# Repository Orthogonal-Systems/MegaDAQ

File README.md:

# MegaDAQ
Data acquisition shield for VMEMega system compatible with arduino mega boards. 16 12b ADCs and 12 12b DACs.

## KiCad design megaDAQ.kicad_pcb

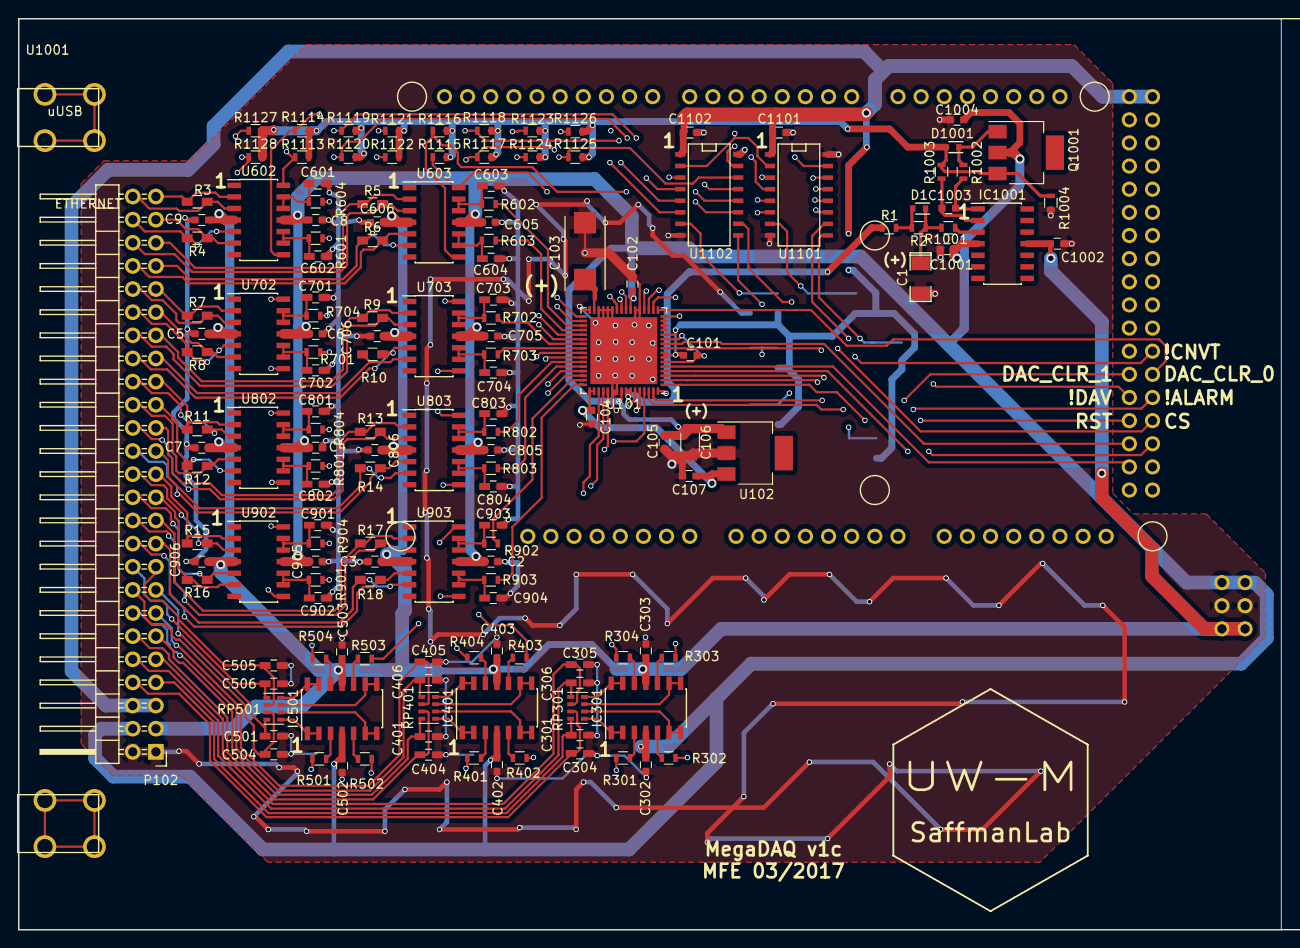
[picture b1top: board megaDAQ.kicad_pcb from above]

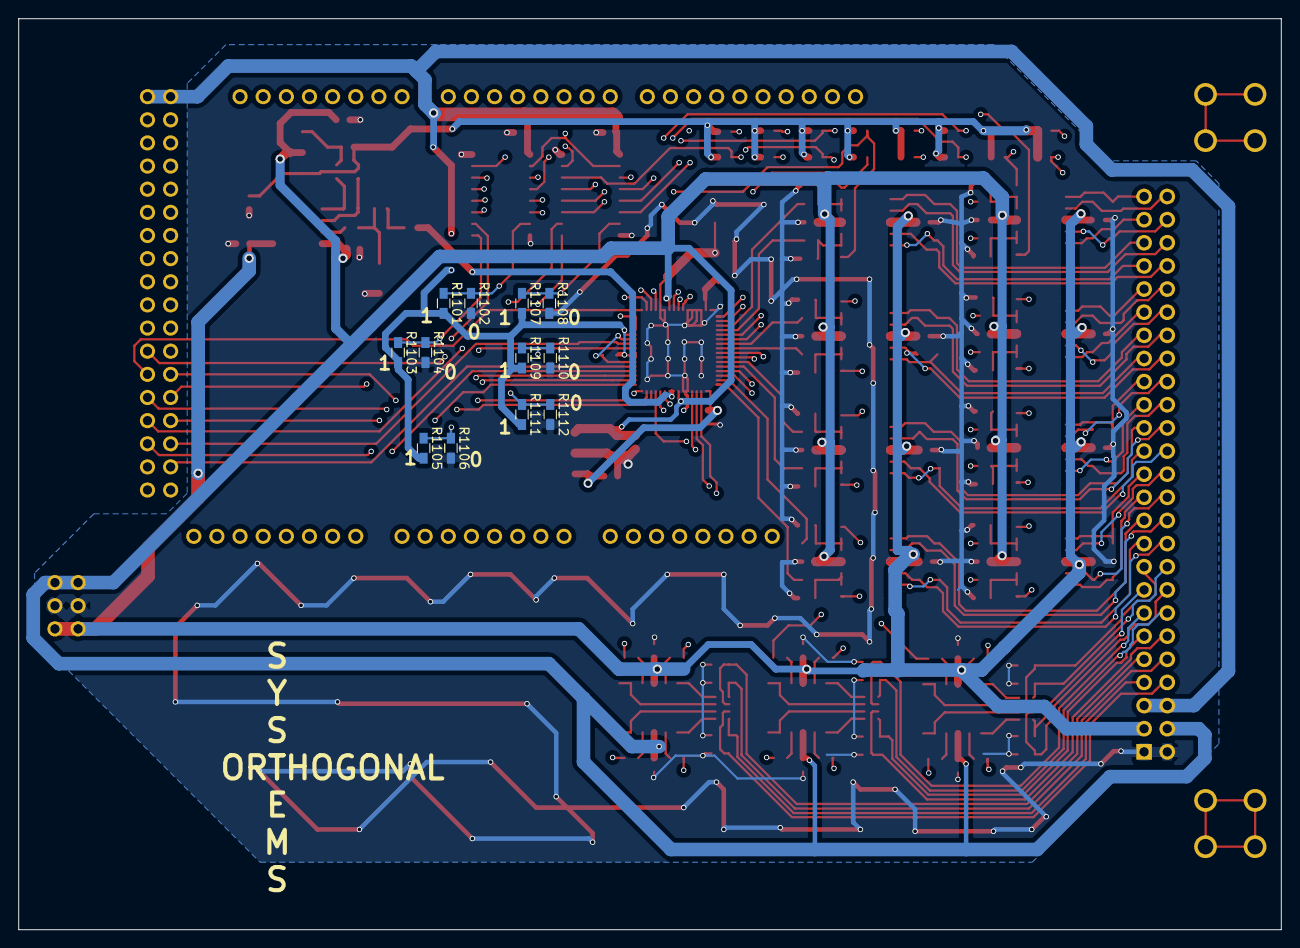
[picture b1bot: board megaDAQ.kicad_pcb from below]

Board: 4 copper layers, 138.6 x 100.0 mm, 168 parts (12 on the bottom side), 161 nets.

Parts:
C1: 15u; SMD-1206_Pol
C2, C3, C4, C5, C6, C7, C8, C9, C101, C102, C104, C105, C107, C302, C303, C402, C403, C502, C503, C605, C606, C705, C706, C805, C806, C905, C906: 0.1u; C_0603
C103: 470u; TantalC_SizeD_EIA-7343_Reflow
C106: 0.33u; C_1206
C301, C304, C305, C306, C401, C404, C405, C406, C501, C504, C505, C506: 10n; C_0603_HandSoldering
C601, C602, C603, C604, C701, C702, C703, C704, C801, C802, C803, C804, C901, C902, C903, C904: 2n; C_0603_HandSoldering
C1001, C1002, C1004, C1101, C1102: 100n; C_0603
C1003: 1n; C_0603
D1, D1001: BAS16; SOD-523
IC301, IC401, IC501, IC1001: MC33079D; SOIC-14_3.9x8.7mm_Pitch1.27mm
P102: CONN_02X25; Pin_Header_Angled_2x25
P105, P106: CONN_01X01; keystone_7773
Q1001: PZT2222A; SOT-223
R1: 698; R_0603
R2, R1004, R1113, R1114, R1115, R1116, R1117, R1118, R1119, R1120, R1121, R1122, R1123, R1124, R1125, R1126, R1127, R1128: 10k; R_0603
R3, R4, R5, R6, R7, R8, R9, R10, R11, R12, R13, R14, R15, R16, R17, R18, R1102, R1103, R1105, R1108, R1109, R1112: DNI; R_0603_HandSoldering
R301, R302, R303, R304, R401, R402, R403, R404, R501, R502, R503, R504, R601, R602, R603, R604, R701, R702, R703, R704, R801, R802, R803, R804, R901, R902, R903, R904, R1001, R1002: 100; R_0603
R1003: 500; R_0603
R1101, R1104, R1106, R1107, R1110, R1111: 0; R_0603_HandSoldering
RP301, RP401, RP501: R_PACK4; R_Cat16-4
U101: AMC7812SPAPR; QFN-64-1EP_9x9mm_Pitch0.5mm
U102: LM78M05CT; SOT-223
U602, U603, U702, U703, U802, U803, U902, U903: diffamp; SOIC-14_3.9x8.7mm_Pitch1.27mm
U1001: VMEMega_no-ICSP2; VMEMegaShield_no-ICSPs
U1101, U1102: TPIC2810; SO-16-N

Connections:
+2V5: R1.2, U101.57, U101.58
+5V: C101.1, C1101.1, C1102.1, P102.5, P102.6, R1101.2, R1103.2, R1105.2, R1107.2, R1109.2, R1111.2, U101.7, U101.8, U101.12, U1001.51, U1001.52, U1101.1, U1102.1
+15V: C2.1, C4.1, C6.1, C8.1, C102.1, C105.1, C106.1, C302.1, C402.1, C502.1, C605.1, C705.1, C805.1, C905.1, C1001.2, C1004.2, IC301.4, IC401.4, IC501.4, IC1001.4, P102.4, Q1001.2, U101.23, U101.56, U102.1, U602.11, U603.11, U702.11, U703.11, U802.11, U803.11, U902.11, U903.11, U1001.87
-15V: C3.2, C5.2, C7.2, C9.2, C303.2, C403.2, C503.2, C606.2, C706.2, C806.2, C906.2, C1002.2, IC301.11, IC401.11, IC501.11, IC1001.11, P102.3, U602.4, U603.4, U702.4, U703.4, U802.4, U803.4, U902.4, U903.4, U1001.89
/!ALARM: U101.62, U1001.78
/!AMC_CS: U101.9, U1001.80
/!AMC_RST: U101.1, U1001.79
/!CNVT: U101.3, U1001.74
/!DAC_CLR_0: U101.17, U1001.76
/!DAC_CLR_1: U101.63, U1001.75
/!DAV: U101.2, U1001.77
/ADC_0: R604.2, U101.33
/ADC_1: R601.2, U101.34
/ADC_2: R602.2, U101.35
/ADC_3: R603.2, U101.36
/ADC_4: R704.2, U101.37
/ADC_5: R701.2, U101.38
/ADC_6: R702.2, U101.39
/ADC_7: R703.2, U101.40
/ADC_8: R804.2, U101.41
/ADC_9: R801.2, U101.42
/ADC_10: R802.2, U101.43
/ADC_11: R803.2, U101.44
/ADC_12: R904.2, U101.45
/ADC_13: R901.2, U101.46
/ADC_14: R902.2, U101.47
/ADC_15: R903.2, U101.48
/ADC_REF: D1001.2, Q1001.3, R1003.1, R1004.2, R1113.1, R1114.1, R1115.1, R1116.1, R1117.2, R1118.2, R1119.2, R1120.2, R1121.1, R1122.1, R1123.1, R1124.1, R1125.2, R1126.2, R1127.2, R1128.2
/AV_DD: C104.1, C107.1, U101.49, U101.50, U102.3
/Ain+0: P102.50, R3.2, U602.3
/Ain+1: P102.48, R4.2, U602.5
/Ain+2: P102.46, R5.2, U603.3
/Ain+3: P102.44, R6.2, U603.5
/Ain+4: P102.42, R7.2, U702.3
/Ain+5: P102.40, R8.2, U702.5
/Ain+6: P102.38, R9.2, U703.3
/Ain+7: P102.36, R10.2, U703.5
/Ain+8: P102.34, R11.2, U802.3
/Ain+9: P102.32, R12.2, U802.5
/Ain+10: P102.30, R13.2, U803.3
/Ain+11: P102.28, R14.2, U803.5
/Ain+12: P102.26, R15.2, U902.3
/Ain+13: P102.24, R16.2, U902.5
/Ain+14: P102.22, R17.2, U903.3
/Ain+15: P102.20, R18.2, U903.5
/Ain-0: P102.49, R3.1, U602.2
/Ain-1: P102.47, R4.1, U602.6
/Ain-2: P102.45, R5.1, U603.2
/Ain-3: P102.43, R6.1, U603.6
/Ain-4: P102.41, R7.1, U702.2
/Ain-5: P102.39, R8.1, U702.6
/Ain-6: P102.37, R9.1, U703.2
/Ain-7: P102.35, R10.1, U703.6
/Ain-8: P102.33, R11.1, U802.2
/Ain-9: P102.31, R12.1, U802.6
/Ain-10: P102.29, R13.1, U803.2
/Ain-11: P102.27, R14.1, U803.6
/Ain-12: P102.25, R15.1, U902.2
/Ain-13: P102.23, R16.1, U902.6
/Ain-14: P102.21, R17.1, U903.2
/Ain-15: P102.19, R18.1, U903.6
/Aout0: C301.1, P102.7, RP301.8
/Aout1: C304.1, P102.8, RP301.7
/Aout2: C305.1, P102.9, RP301.6
/Aout3: C306.1, P102.10, RP301.5
/Aout4: C401.1, P102.11, RP401.8
/Aout5: C404.1, P102.12, RP401.7
/Aout6: C405.1, P102.13, RP401.6
/Aout7: C406.1, P102.14, RP401.5
/Aout8: C501.1, P102.15, RP501.8
/Aout9: C504.1, P102.16, RP501.7
/Aout10: C505.1, P102.17, RP501.6
/Aout11: C506.1, P102.18, RP501.5
/DAC_0: R301.1, U101.26
/DAC_1: R302.1, U101.25
/DAC_2: R303.1, U101.24
/DAC_3: R304.1, U101.20
/DAC_4: R401.1, U101.19
/DAC_5: R402.1, U101.18
/DAC_6: R403.1, U101.51
/DAC_7: R404.1, U101.52
/DAC_8: R501.1, U101.53
/DAC_9: R502.1, U101.59
/DAC_10: R503.1, U101.60
/DAC_11: R504.1, U101.61
/MISO: U101.10, U1001.81
/MOSI: U101.4, U1001.82
/SCK: U101.5, U1001.83
/SCL: U1001.25, U1101.15, U1102.15
/SDA: U1001.26, U1101.2, U1102.2
/Sheet57BE2601/Ain_os0: R1113.2, U602.14, U1101.3
/Sheet57BE2601/Ain_os1: R1114.2, U602.8, U1101.4
/Sheet57BE2601/Ain_os2: R1115.2, U603.14, U1101.5
/Sheet57BE2601/Ain_os3: R1116.2, U603.8, U1101.6
/Sheet57BE2601/Ain_os4: R1120.1, U702.14, U1101.11
/Sheet57BE2601/Ain_os5: R1119.1, U702.8, U1101.12
/Sheet57BE2601/Ain_os6: R1118.1, U703.14, U1101.13
/Sheet57BE2601/Ain_os7: R1117.1, U703.8, U1101.14
/Sheet57BE2601/Ain_os8: R1121.2, U802.14, U1102.3
/Sheet57BE2601/Ain_os9: R1122.2, U802.8, U1102.4
/Sheet57BE2601/Ain_os10: R1123.2, U803.14, U1102.5
/Sheet57BE2601/Ain_os11: R1124.2, U803.8, U1102.6
/Sheet57BE2601/Ain_os12: R1128.1, U902.14, U1102.11
/Sheet57BE2601/Ain_os13: R1127.1, U902.8, U1102.12
/Sheet57BE2601/Ain_os14: R1126.1, U903.14, U1102.13
/Sheet57BE2601/Ain_os15: R1125.1, U903.8, U1102.14
GNDA: C1.2, C2.2, C3.1, C4.2, C5.1, C6.2, C7.1, C8.2, C9.1, C102.2, C103.2, C104.2, C105.2, C106.2, C107.2, C301.2, C302.2, C303.1, C304.2, C305.2, C306.2, C401.2, C402.2, C403.1, C404.2, C405.2, C406.2, C501.2, C502.2, C503.1, C504.2, C505.2, C506.2, C601.2, C602.2, C603.2, C604.2, C605.2, C606.1, C701.2, C702.2, C703.2, C704.2, C705.2, C706.1, C801.2, C802.2, C803.2, C804.2, C805.2, C806.1, C901.2, C902.2, C903.2, C904.2, C905.2, C906.1, C1001.1, C1002.1, C1004.1, C1101.2, C1102.2, P102.1, P102.2, R1004.1, R1102.2, R1104.2, R1106.2, R1108.2, R1110.2, R1112.2, U101.21, U101.22, U101.27, U101.28, U101.29, U101.30, U101.32, U101.54, U101.55, U101.65, U102.2, U1001.88, U1101.8, U1101.16, U1102.8, U1102.16
GNDD: C101.2, U101.6, U101.11, U101.13, U101.14, U101.15, U101.16, U101.64, U1001.85, U1001.86
unnamed: C1.1, D1.1, R2.1, R1001.2
unnamed: C103.1, U101.31
unnamed: C601.1, R604.1, U602.12, U602.13
unnamed: C602.1, R601.1, U602.9, U602.10
unnamed: C603.1, R602.1, U603.12, U603.13
unnamed: C604.1, R603.1, U603.9, U603.10
unnamed: C701.1, R704.1, U702.12, U702.13
unnamed: C702.1, R701.1, U702.9, U702.10
unnamed: C703.1, R702.1, U703.12, U703.13
unnamed: C704.1, R703.1, U703.9, U703.10
unnamed: C801.1, R804.1, U802.12, U802.13
unnamed: C802.1, R801.1, U802.9, U802.10
unnamed: C803.1, R802.1, U803.12, U803.13
unnamed: C804.1, R803.1, U803.9, U803.10
unnamed: C901.1, R904.1, U902.12, U902.13
unnamed: C902.1, R901.1, U902.9, U902.10
unnamed: C903.1, R902.1, U903.12, U903.13
unnamed: C904.1, R903.1, U903.9, U903.10
unnamed: C1003.1, IC1001.1, R1002.2
unnamed: C1003.2, IC1001.2, R1003.2
unnamed: D1.2, R1.1, R2.2
unnamed: D1001.1, Q1001.1, R1002.1
unnamed: IC301.1, IC301.2, RP301.1
unnamed: IC301.3, R301.2
unnamed: IC301.5, R302.2
unnamed: IC301.6, IC301.7, RP301.2
unnamed: IC301.8, IC301.9, RP301.3
unnamed: IC301.10, R303.2
unnamed: IC301.12, R304.2
unnamed: IC301.13, IC301.14, RP301.4
unnamed: IC401.1, IC401.2, RP401.1
unnamed: IC401.3, R401.2
unnamed: IC401.5, R402.2
unnamed: IC401.6, IC401.7, RP401.2
unnamed: IC401.8, IC401.9, RP401.3
unnamed: IC401.10, R403.2
unnamed: IC401.12, R404.2
unnamed: IC401.13, IC401.14, RP401.4
unnamed: IC501.1, IC501.2, RP501.1
unnamed: IC501.3, R501.2
unnamed: IC501.5, R502.2
unnamed: IC501.6, IC501.7, RP501.2
unnamed: IC501.8, IC501.9, RP501.3
unnamed: IC501.10, R503.2
unnamed: IC501.12, R504.2
unnamed: IC501.13, IC501.14, RP501.4
unnamed: IC1001.3, R1001.1
unnamed: R1101.1, R1102.1, U1101.7
unnamed: R1103.1, R1104.1, U1101.9
unnamed: R1105.1, R1106.1, U1101.10
unnamed: R1107.1, R1108.1, U1102.7
unnamed: R1109.1, R1110.1, U1102.9
unnamed: R1111.1, R1112.1, U1102.10

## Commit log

2016-05-02 v1 revb
2017-05-03 commiting version v1c, produced
